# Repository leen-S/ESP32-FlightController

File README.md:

# ESP32 Flight Controller

## Overview

This repository contains all the necessary files for the **ESP32 Flight Controller** project. Designed for educational and practical purposes, this project showcases how an ESP32 microcontroller can be used to develop a flight controller. It includes firmware, schematics, PCB designs, and manufacturing files to bring the project to life.

---

## Repository Structure

### 1. **ESP32-Flight-Controller--main**
This folder contains:
- **Code**: The firmware written for the ESP32 microcontroller to manage and control the drone's operations.
- **Schematics**: Circuit diagrams detailing the hardware connections and design.

### 2. **PCB Designs/KiCAD**
This folder contains:
- **Sketches**: Conceptual sketches of the PCB layout.
- **PCB Layout**: The complete PCB design created using KiCAD.
- **Manufacturing and Gerber Files**: Files required for manufacturing the PCB, including drill files, silkscreen layers, and solder masks.

---

## How to Use

### 1. **Setup and Prerequisites**
- Install the necessary tools:
  - Arduino IDE (or PlatformIO) for uploading the firmware.
  - KiCAD for viewing and editing PCB designs.
- Ensure you have an ESP32 Dev Kit and other necessary components as specified in the schematics.

### 2. **Firmware Installation**
- Navigate to the `ESP32-Flight-Controller--main` folder.
- Open the provided `.ino` or equivalent firmware file in your IDE.
- Configure the project-specific parameters (e.g., pin mappings and calibration values).
- Upload the firmware to the ESP32 using a USB connection.

### 3. **PCB Manufacturing**
- Navigate to the `PCB Designs/KiCAD` folder.
- Use the Gerber files to manufacture the PCB:
  - Upload them to a PCB manufacturer (e.g., JLCPCB, PCBWay).
- Assemble the components as per the provided schematics.

---

## Features
- **ESP32-based Control**: Utilizes the ESP32 microcontroller for real-time flight control.
- **Modular Design**: The project is organized into distinct files for ease of use and modification.
- **Custom PCB**: Designed using KiCAD for a compact and efficient layout.
- **Open Source**: Fully customizable and adaptable for different applications.

---

## Acknowledgment
Special thanks to **@pratikphadte** for making amazing videos.

---

## Contributing
Contributions are welcome! Feel free to:
- Submit bug reports or feature requests via the Issues tab.
- Fork the repository and submit pull requests with improvements.

---

## License
This project is licensed under the [MIT License](LICENSE). You are free to use, modify, and distribute the code and designs with proper attribution.

---

## Contact
For questions or collaboration, reach out via:
- **Email**: neelalohitk@gmail.com
- **LinkedIn**: https://www.linkedin.com/in/neelalohit-korlhalli/

---

Happy Building! 🚀

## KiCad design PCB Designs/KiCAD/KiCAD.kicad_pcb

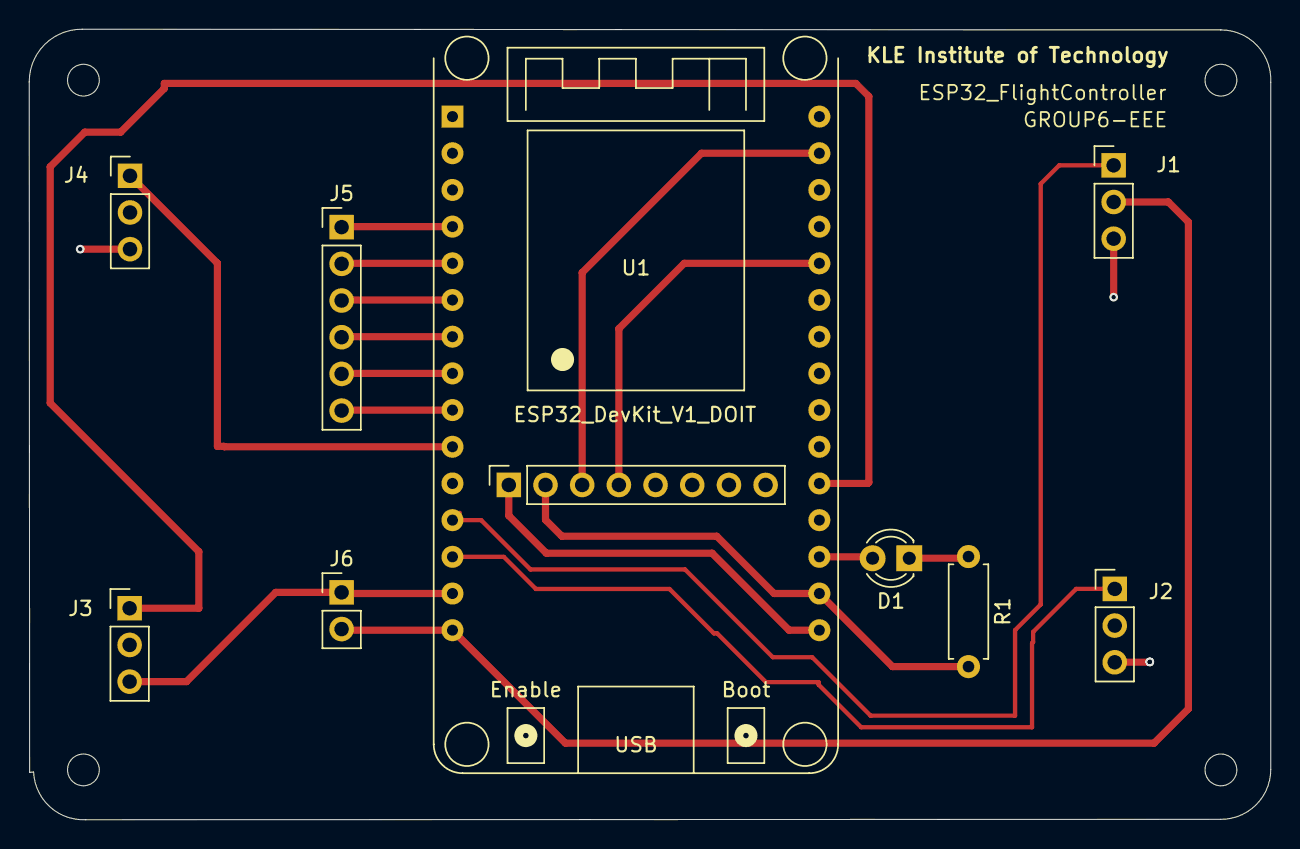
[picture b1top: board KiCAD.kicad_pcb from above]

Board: 2 copper layers, 86.0 x 54.7 mm, 14 parts (0 on the bottom side), 17 nets.

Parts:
D1: LED; LED_D3.0mm
H1, H2, H3, H4: MountingHole; MountingHole_2.2mm_M2
J1, J2, J3, J4: Conn_01x03_Pin; PinHeader_1x03_P2.54mm_Vertical
J5: Conn_01x06_Pin; PinHeader_1x06_P2.54mm_Vertical
J6: Conn_01x02_Pin; PinHeader_1x02_P2.54mm_Vertical
J7: Conn_01x08_Socket; PinSocket_1x08_P2.54mm_Vertical
R1: 220; R_Axial_DIN0207_L6.3mm_D2.5mm_P7.62mm_Horizontal
U1: ESP32_DevKit_V1_DOIT; esp32_devkit_v1_doit

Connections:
/S1: J1.1, U1.12 (IO12)
/S2: J2.1, U1.13 (IO13)
/S3: J3.1, U1.20 (IO4)
/S4: J4.1, U1.10 (IO27)
/T1: J5.1, U1.4 (IO34)
/T2: J5.2, U1.5 (IO35)
/T3: J5.3, U1.6 (IO32)
/T4: J5.4, U1.7 (IO33)
/T5: J5.5, U1.8 (IO25)
/T6: J5.6, U1.9 (IO26)
/VIN: J1.2, J6.2, U1.15 (VIN)
GND: J1.3, J2.3, J3.3, J4.3, J6.1, J7.2, R1.2, U1.14 (GND), U1.17 (GND)
unnamed: D1.2 (A), U1.18 (IO15)
unnamed: D1.1 (K), R1.1
SCL: J7.3, U1.29 (IO22)
SDA: J7.4, U1.26 (IO21)
VCC: J7.1, U1.16 (3V3)
